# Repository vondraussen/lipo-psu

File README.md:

# LIPO PSU
2S lithium polymer battery power supply for micro controller projects. The main idea is to use it for long running low power micro controller projects.

This is work in progress...

## Requirements
- Voltage output 3.3 V
- Current ouput up to 500 mA
- low quiescent current < 10 uA
- cell protection
- discharge/undervoltage protection

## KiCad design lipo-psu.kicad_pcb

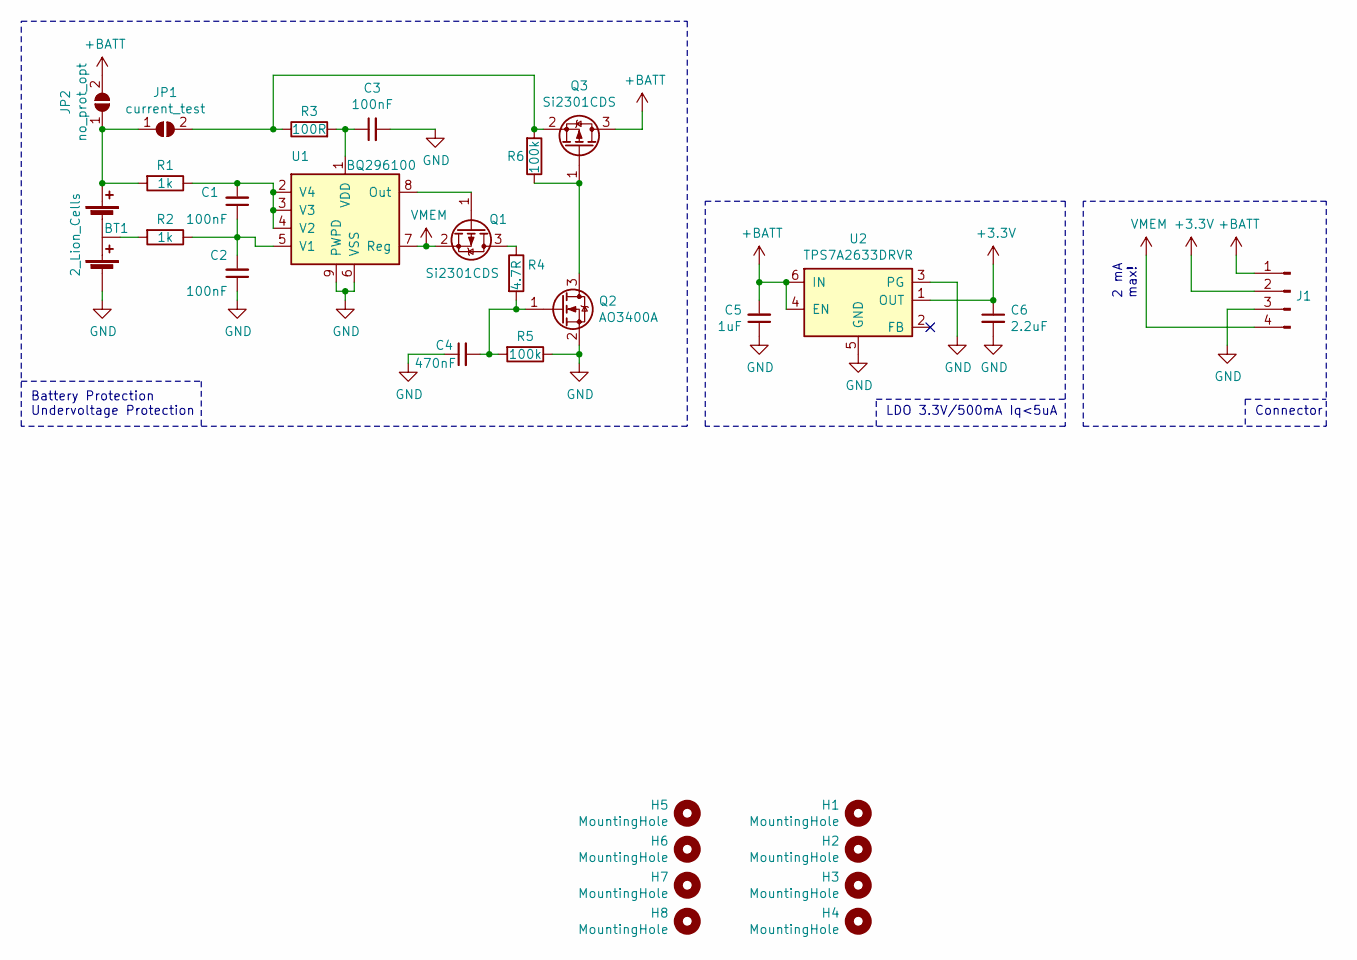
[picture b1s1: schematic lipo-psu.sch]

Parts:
BT1: 2_Lion_Cells; BatteryHolder_Keystone_1048P_2x18650; Digikey 36-1048P-ND
C1, C2, C3: 100nF; C_0603_1608Metric; JLCPCB CC0603KRX7R9BB104
C4: 470nF; C_0603_1608Metric; JLCPCB CL10B474KA8NNNC
C5: 1uF; C_0603_1608Metric; JLCPCB CL10A105KB8NNNC
C6: 2.2uF; C_1206_3216Metric; JLCPCB CL31B225KBHNNNE
H1, H2, H3, H4, H5, H6, H7, H8: MountingHole; MountingHole_2.5mm
J1: 4Pin; PinHeader_1x04_P2.54mm_Vertical
JP1: current_test; SolderJumper-2_P1.3mm_Open_TrianglePad1.0x1.5mm
JP2: no_prot_opt; SolderJumper-2_P1.3mm_Open_TrianglePad1.0x1.5mm
Q1, Q3: Si2301CDS; SOT-23; JLCPCB SI2301CDS-T1-GE3
Q2: AO3400A; SOT-23; JLCPCB AO3400A
R1, R2: 1k; R_0603_1608Metric; JLCPCB 0603WAF1001T5E
R3: 100R; R_0603_1608Metric; JLCPCB 0603WAF1000T5E
R4: 4.7R; R_0603_1608Metric; JLCPCB 0603WAF470KT5E
R5, R6: 100k; R_0603_1608Metric; JLCPCB 0603WAF1003T5E
U1: BQ296100; WSON-8-1EP_2x2mm_P0.5mm_EP0.9x1.6mm; Digikey 296-50964-1-ND
U2: TPS7A2633DRVR; WSON-6-1EP_2x2mm_P0.65mm_EP1x1.6mm; Digikey 296-TPS7A2633DRVRCT-ND

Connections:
+3V3: C6.1, J1.2, U2.1 (OUT)
+BATT: C5.2, J1.1, JP2.2 (B), Q3.3 (D), U2.4 (EN), U2.6 (IN)
GND: BT1.3 (-), C2.1, C3.2, C4.1, C5.1, C6.2, J1.3, Q2.2 (S), R5.1, U1.6 (VSS), U1.9 (PWPD), U2.3 (PG), U2.5 (GND), U2.7 (GND)
unnamed: BT1.1 (+), JP1.1 (A), JP2.1 (A), R1.2
unnamed: BT1.2 (-), BT1.4 (+), R2.2
unnamed: C1.1, C2.2, R2.1, U1.5 (V1)
unnamed: C1.2, R1.1, U1.2 (V4), U1.3 (V3), U1.4 (V2)
unnamed: C3.1, R3.2, U1.1 (VDD)
unnamed: C4.2, Q2.1 (G), R4.2, R5.2
unnamed: JP1.2 (B), Q3.2 (S), R3.1, R6.2
unnamed: Q1.1 (G), U1.8 (Out)
unnamed: Q1.3 (D), R4.1
unnamed: Q2.3 (D), Q3.1 (G), R6.1
VMEM: J1.4, Q1.2 (S), U1.7 (Reg)

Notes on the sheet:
LDO 3.3V/500mA Iq<5uA
Battery Protection Undervoltage Protection
2 mA max!
Connector

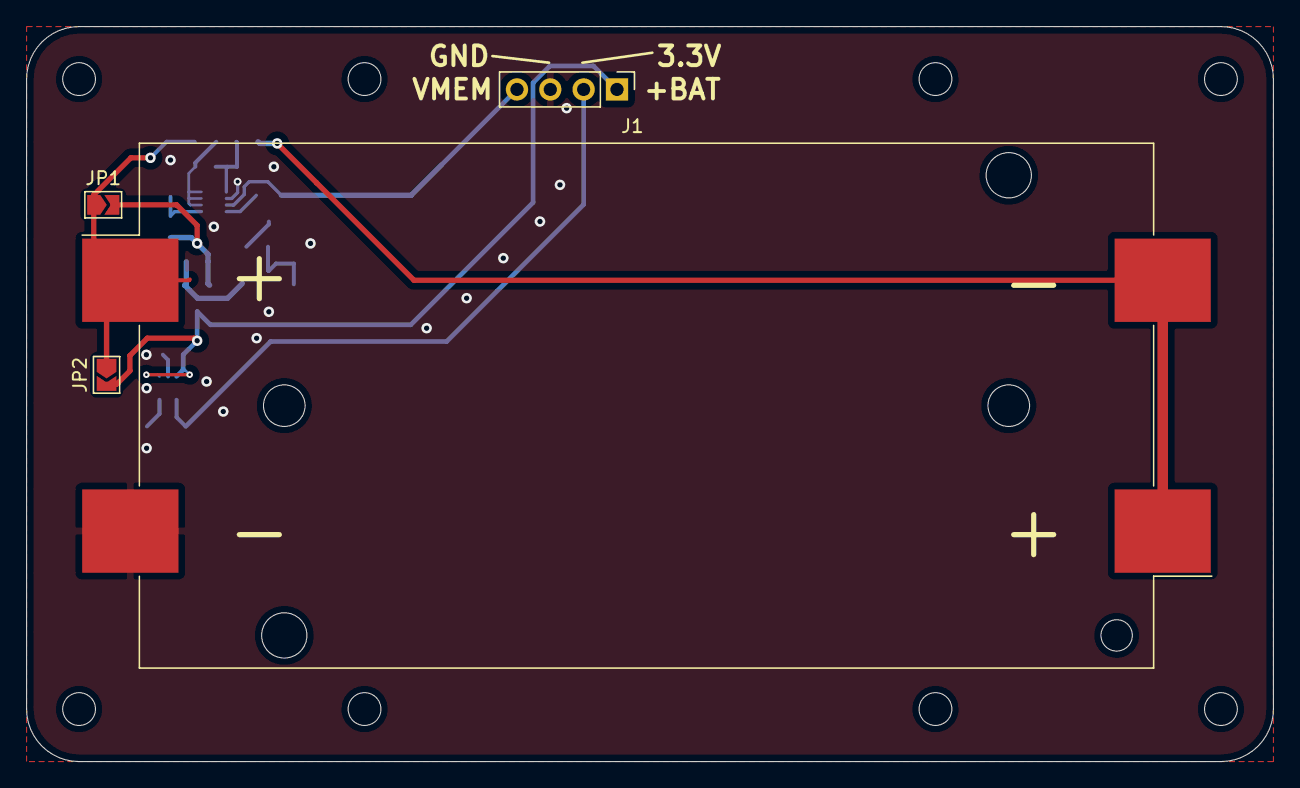
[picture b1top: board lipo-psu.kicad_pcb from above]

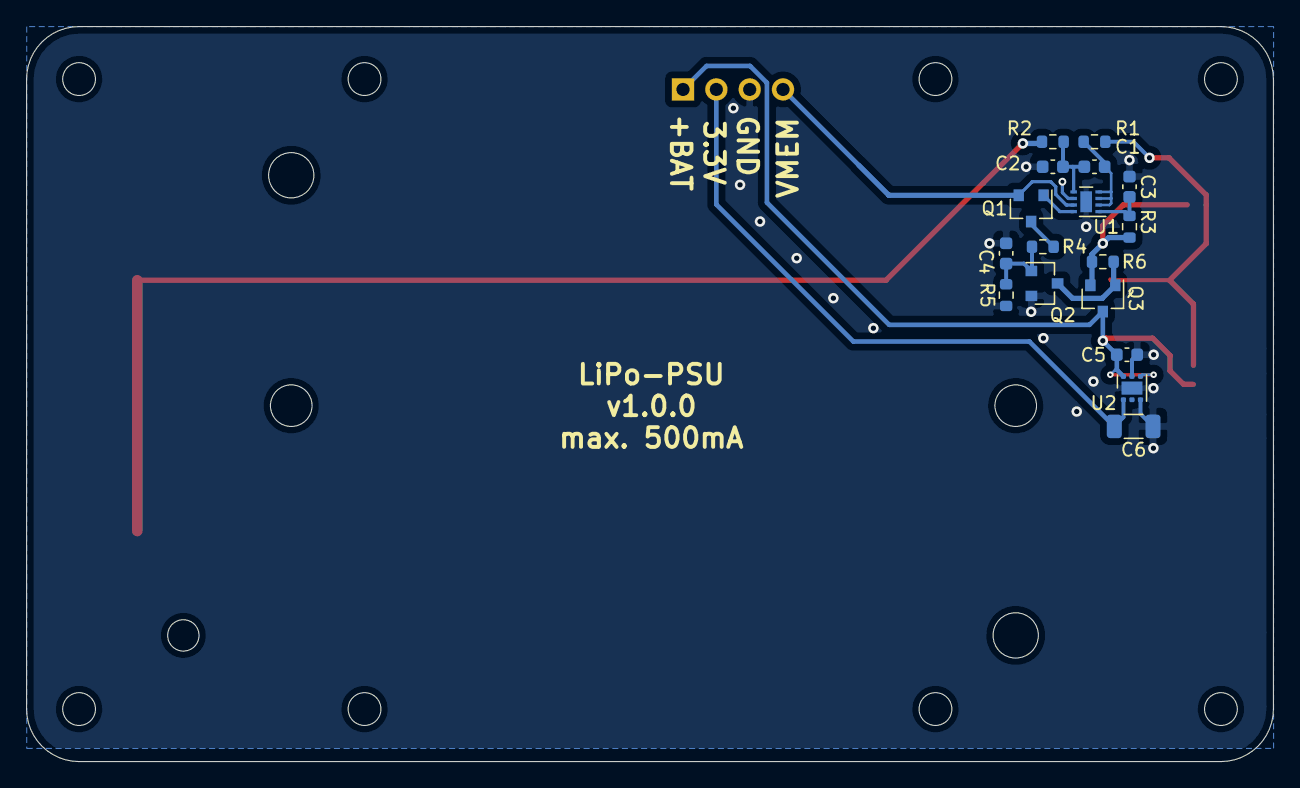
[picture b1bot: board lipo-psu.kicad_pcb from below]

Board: 2 copper layers, 95.0 x 56.0 mm, 29 parts (17 on the bottom side), 14 nets.

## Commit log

2021-01-07 init commit
2021-02-18 add kibot configs
